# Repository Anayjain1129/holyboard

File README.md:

# Orpheus-Pad

### Why did I make it?
I made it because I want keeb so bed and my keyboar has stop working😭, So, I though I can make it through highway.

### What was the hardest part about this ?
Getting two keebs rejected was the hardest part I hope this one get approved.

Features:

- OLED for Capslock and numpad
- 80x keys
- Raspberry Pi Pico
- Customised layout
- QMK firmware
- HackClub Branded PCB
- Custom case

### Schematic

### PCB 

### Case

The space which is remaining and is empty is intetional cause i will be using stickers there

- Side

I made some asthetics for my custom keeb. Like I have added holes on all the sides to make it look more good

### 3D view of all parts together 

link to full 3d thing-
https://cad.onshape.com/documents/cac1d933657028d584a203ec/w/4e6a3fc25500be93378999df/e/b6dbc2fcb8cb6ab38fa48a89?renderMode=0&uiState=688a702c2d96e6706e64265e

A special thanks to Kai, Aditya, Mohid and The-Wolf and big thanks to alex who is helping me to make my projects better. 💓

## BOM

| Name                                                          | Qty | Final Price - INR (USD) | Link                                                                                                                        |
| ------------------------------------------------------------- | --- | ----------------------- | ----------------------------------------------------------------------------------------------------------                  |
| Gateron EF Grayish                                            | 80  | 1560 ($18.19)           | [here](https://neomacro.in/products/gateron-ef-grayish)                                                                     |
| Durock Smokey Screw-In Stabilizers V2 (4+1 w/ 6.25u spacebar) | 1   | 1590 ($18.58)           | [here](https://stackskb.com/store/durock-smokey-screw-in-stabilizers-v2/)                                                   |
| Cherry Profile PBT Keycaps                                    | 1   | 1300 ($15.15)           | [here](https://stackskb.com/store/veekos-gradient-keycaps-cherry-profile-135-keys)                                          |
| Diode 1N4148 Through - Hole                                   | 100 | 100 ($1.17)             | [here](https://amzn.in/d/j3eLvoh)                                                                                           |
| OLED                                                          | 1   | 166 ($1.92)             | [here]([https://amzn.in/d/hVRxzij](https://www.amazon.in/Electronic-Spices-Display-Module-Interface/dp/B0D9S3W7VM/ref=sr_1_8?sr=8-8))                                                                                           |
| M3 x 20mm Bolt                                                | 15  | 149 ($1.73)             | [here](https://amzn.in/d/8GRQWAB)                                                                                           |
| M3 Nuts                                                       | 8   | 100 ($1.16)             | [here](https://amzn.in/d/7UQtsm8)                                                                                           |
| M3 x 5mm Heatset Insert                                       | 25  | 179 ($2.09)             | [here](https://amzn.in/d/ixybuAc)                                                                                           |
| PCB - (Black Color)                                           | 5   | 6037 ($69.99)           ||
| Raspberry Pi Pico                                             | 1   | 449 ($5.19)             | [here](http://amazon.in/Raspberry-Pi-Headers-Soldered-Micro/dp/B08WPNM7JB/ref=sr_1_2?sr=8-2)                                |
| Case- top,mid,bot                                             | 1   | Print Legion

## Total Pricing
The total price comes out to be 11,660.13 INR ($135.17)

The pricing might slightly vary due to flash sales, and dollar market trends.

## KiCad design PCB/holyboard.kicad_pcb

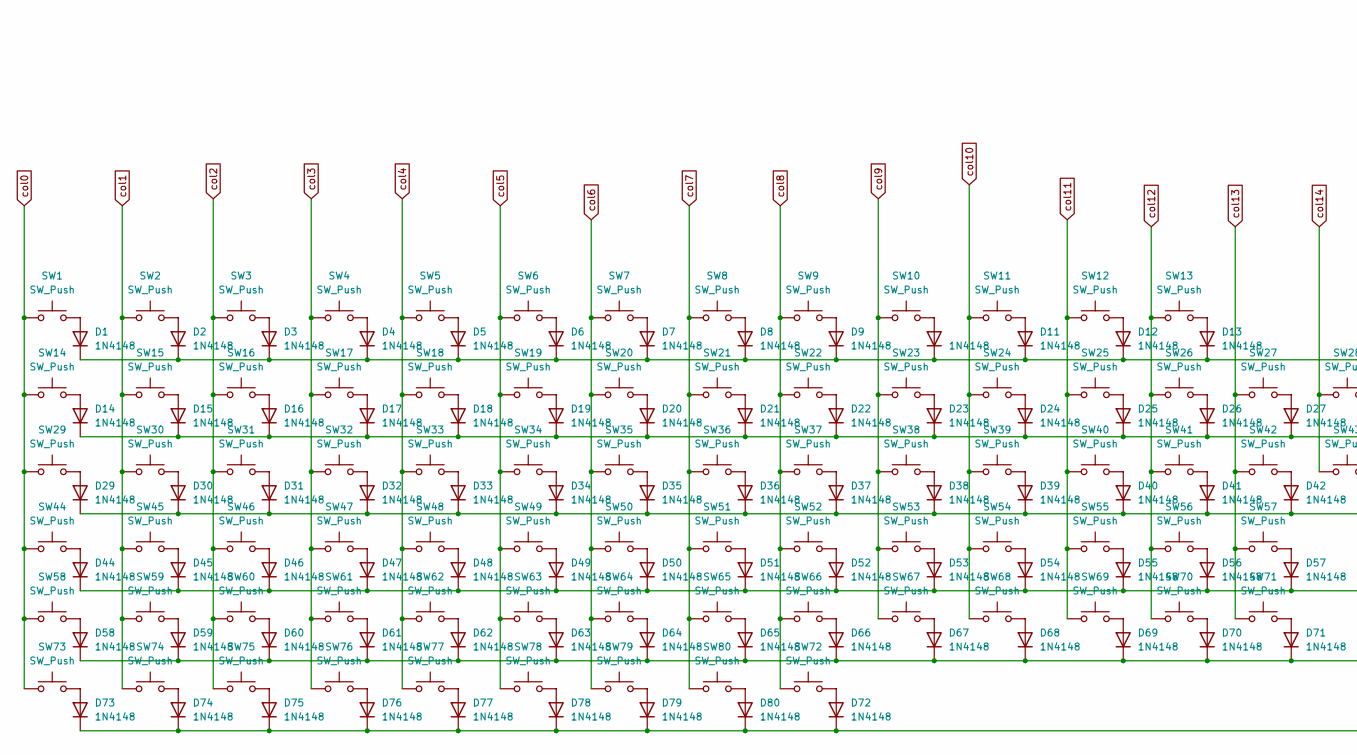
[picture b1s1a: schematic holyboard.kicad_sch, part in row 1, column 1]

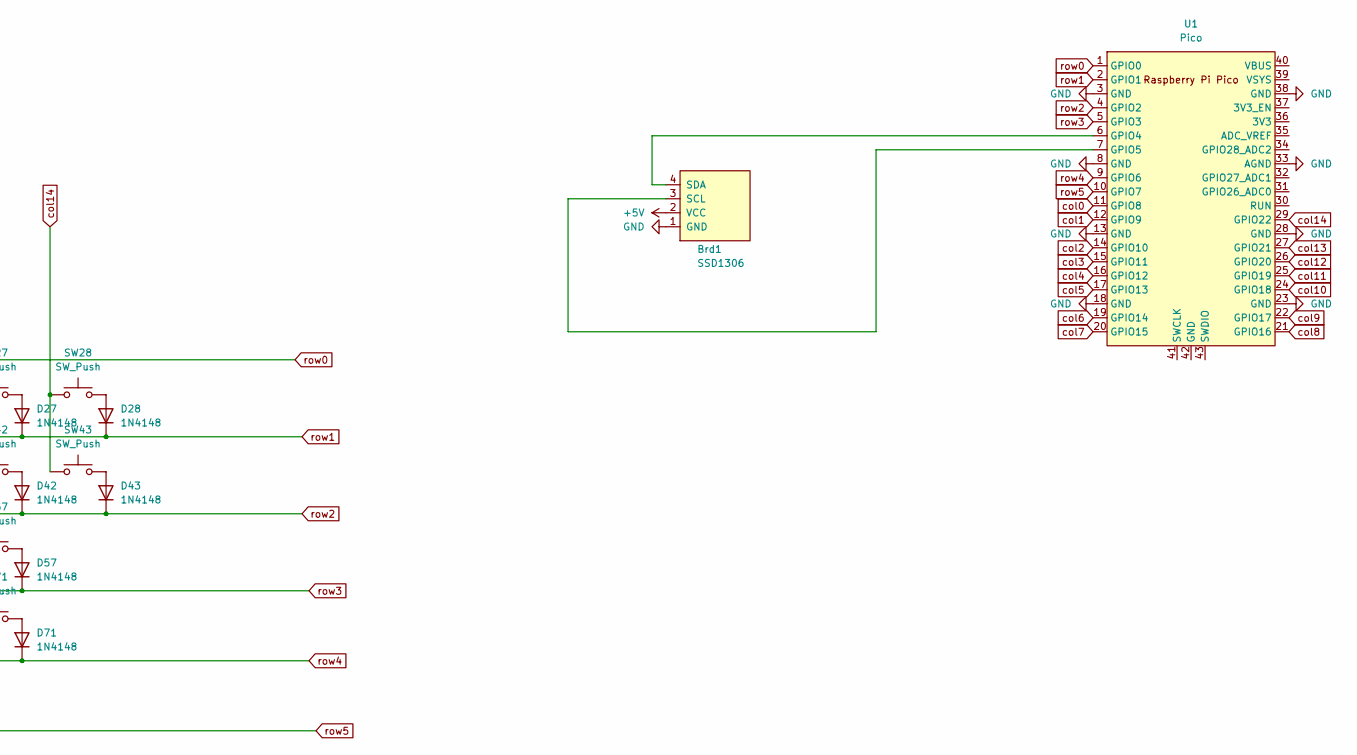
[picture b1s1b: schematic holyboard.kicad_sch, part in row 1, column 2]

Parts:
Brd1: SSD1306; SSD1306-0.91-OLED-4pin-128x32
D1, D2, D3, D4, D5, D6, D7, D8, D9, D10, D11, D12, D13, D14, D15, D16, D17, D18, D19, D20, D21, D22, D23, D24, D25, D26, D27, D28, D29, D30, D31, D32, D33, D34, D35, D36, D37, D38, D39, D40, D41, D42, D43, D44, D45, D46, D47, D48, D49, D50, D51, D52, D53, D54, D55, D56, D57, D58, D59, D60, D61, D62, D63, D64, D65, D66, D67, D68, D69, D70, D71, D72, D73, D74, D75, D76, D77, D78, D79, D80: 1N4148; D_DO-35_SOD27_P7.62mm_Horizontal
SW1, SW2, SW3, SW4, SW5, SW6, SW7, SW8, SW9, SW10, SW11, SW12, SW13, SW14, SW15, SW16, SW17, SW18, SW19, SW20, SW21, SW22, SW23, SW24, SW25, SW26, SW28, SW30, SW31, SW32, SW33, SW34, SW35, SW36, SW37, SW38, SW39, SW40, SW41, SW43, SW45, SW46, SW47, SW48, SW49, SW50, SW51, SW52, SW53, SW54, SW55, SW57, SW59, SW60, SW61, SW62, SW63, SW64, SW65, SW66, SW67, SW68, SW70, SW71, SW78, SW79, SW80: SW_Push; SW_Cherry_MX_1.00u_PCB
SW27: SW_Push; SW_Cherry_MX_2.00u_PCB
SW29, SW42: SW_Push; SW_Cherry_MX_1.50u_PCB
SW44, SW69: SW_Push; SW_Cherry_MX_1.75u_PCB
SW56, SW58: SW_Push; SW_Cherry_MX_2.25u_PCB
SW72, SW73, SW74, SW76, SW77: SW_Push; SW_Cherry_MX_1.25u_PCB
SW75: SW_Push; SW_Cherry_MX_6.25u_PCB
U1: Pico; RPi_Pico_SMD_TH

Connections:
+5V: Brd1.2 (VCC)
GND: Brd1.1 (GND), U1.3 (GND), U1.8 (GND), U1.13 (GND), U1.18 (GND), U1.23 (GND), U1.28 (GND), U1.33 (AGND), U1.38 (GND)
unnamed: Brd1.3 (SCL), U1.7 (GPIO5)
unnamed: Brd1.4 (SDA), U1.6 (GPIO4)
unnamed: D1.2 (A), SW1.2
unnamed: D2.2 (A), SW2.2
unnamed: D3.2 (A), SW3.2
unnamed: D4.2 (A), SW4.2
unnamed: D5.2 (A), SW5.2
unnamed: D6.2 (A), SW6.2
unnamed: D7.2 (A), SW7.2
unnamed: D8.2 (A), SW8.2
unnamed: D9.2 (A), SW9.2
unnamed: D10.2 (A), SW10.2
unnamed: D11.2 (A), SW11.2
unnamed: D12.2 (A), SW12.2
unnamed: D13.2 (A), SW13.2
unnamed: D14.2 (A), SW14.2
unnamed: D15.2 (A), SW15.2
unnamed: D16.2 (A), SW16.2
unnamed: D17.2 (A), SW17.2
unnamed: D18.2 (A), SW18.2
unnamed: D19.2 (A), SW19.2
unnamed: D20.2 (A), SW20.2
unnamed: D21.2 (A), SW21.2
unnamed: D22.2 (A), SW22.2
unnamed: D23.2 (A), SW23.2
unnamed: D24.2 (A), SW24.2
unnamed: D25.2 (A), SW25.2
unnamed: D26.2 (A), SW26.2
unnamed: D27.2 (A), SW27.2
unnamed: D28.2 (A), SW28.2
unnamed: D29.2 (A), SW29.2
unnamed: D30.2 (A), SW30.2
unnamed: D31.2 (A), SW31.2
unnamed: D32.2 (A), SW32.2
unnamed: D33.2 (A), SW33.2
unnamed: D34.2 (A), SW34.2
unnamed: D35.2 (A), SW35.2
unnamed: D36.2 (A), SW36.2
unnamed: D37.2 (A), SW37.2
unnamed: D38.2 (A), SW38.2
unnamed: D39.2 (A), SW39.2
unnamed: D40.2 (A), SW40.2
unnamed: D41.2 (A), SW41.2
unnamed: D42.2 (A), SW42.2
unnamed: D43.2 (A), SW43.2
unnamed: D44.2 (A), SW44.2
unnamed: D45.2 (A), SW45.2
unnamed: D46.2 (A), SW46.2
unnamed: D47.2 (A), SW47.2
unnamed: D48.2 (A), SW48.2
unnamed: D49.2 (A), SW49.2
unnamed: D50.2 (A), SW50.2
unnamed: D51.2 (A), SW51.2
unnamed: D52.2 (A), SW52.2
unnamed: D53.2 (A), SW53.2
unnamed: D54.2 (A), SW54.2
unnamed: D55.2 (A), SW55.2
unnamed: D56.2 (A), SW56.2
unnamed: D57.2 (A), SW57.2
unnamed: D58.2 (A), SW58.2
unnamed: D59.2 (A), SW59.2
unnamed: D60.2 (A), SW60.2
unnamed: D61.2 (A), SW61.2
unnamed: D62.2 (A), SW62.2
unnamed: D63.2 (A), SW63.2
unnamed: D64.2 (A), SW64.2
unnamed: D65.2 (A), SW65.2
unnamed: D66.2 (A), SW66.2
unnamed: D67.2 (A), SW67.2
unnamed: D68.2 (A), SW68.2
unnamed: D69.2 (A), SW69.2
unnamed: D70.2 (A), SW70.2
unnamed: D71.2 (A), SW71.2
unnamed: D72.2 (A), SW72.2
unnamed: D73.2 (A), SW73.2
unnamed: D74.2 (A), SW74.2
unnamed: D75.2 (A), SW75.2
unnamed: D76.2 (A), SW76.2
unnamed: D77.2 (A), SW77.2
unnamed: D78.2 (A), SW78.2
unnamed: D79.2 (A), SW79.2
unnamed: D80.2 (A), SW80.2
col0: SW1.1, SW14.1, SW29.1, SW44.1, SW58.1, SW73.1, U1.11 (GPIO8)
col1: SW2.1, SW15.1, SW30.1, SW45.1, SW59.1, SW74.1, U1.12 (GPIO9)
col2: SW3.1, SW16.1, SW31.1, SW46.1, SW60.1, SW75.1, U1.14 (GPIO10)
col3: SW4.1, SW17.1, SW32.1, SW47.1, SW61.1, SW76.1, U1.15 (GPIO11)
col4: SW5.1, SW18.1, SW33.1, SW48.1, SW62.1, SW77.1, U1.16 (GPIO12)
col5: SW6.1, SW19.1, SW34.1, SW49.1, SW63.1, SW78.1, U1.17 (GPIO13)
col6: SW7.1, SW20.1, SW35.1, SW50.1, SW64.1, SW79.1, U1.19 (GPIO14)
col7: SW8.1, SW21.1, SW36.1, SW51.1, SW65.1, SW80.1, U1.20 (GPIO15)
col8: SW9.1, SW22.1, SW37.1, SW52.1, SW66.1, SW72.1, U1.21 (GPIO16)
col9: SW10.1, SW23.1, SW38.1, SW53.1, SW67.1, U1.22 (GPIO17)
col10: SW11.1, SW24.1, SW39.1, SW54.1, SW68.1, U1.24 (GPIO18)
col11: SW12.1, SW25.1, SW40.1, SW55.1, SW69.1, U1.25 (GPIO19)
col12: SW13.1, SW26.1, SW41.1, SW56.1, SW70.1, U1.26 (GPIO20)
col13: SW27.1, SW42.1, SW57.1, SW71.1, U1.27 (GPIO21)
col14: SW28.1, SW43.1, U1.29 (GPIO22)
row0: D1.1 (K), D2.1 (K), D3.1 (K), D4.1 (K), D5.1 (K), D6.1 (K), D7.1 (K), D8.1 (K), D9.1 (K), D10.1 (K), D11.1 (K), D12.1 (K), D13.1 (K), U1.1 (GPIO0)
row1: D14.1 (K), D15.1 (K), D16.1 (K), D17.1 (K), D18.1 (K), D19.1 (K), D20.1 (K), D21.1 (K), D22.1 (K), D23.1 (K), D24.1 (K), D25.1 (K), D26.1 (K), D27.1 (K), D28.1 (K), U1.2 (GPIO1)
row2: D29.1 (K), D30.1 (K), D31.1 (K), D32.1 (K), D33.1 (K), D34.1 (K), D35.1 (K), D36.1 (K), D37.1 (K), D38.1 (K), D39.1 (K), D40.1 (K), D41.1 (K), D42.1 (K), D43.1 (K), U1.4 (GPIO2)
row3: D44.1 (K), D45.1 (K), D46.1 (K), D47.1 (K), D48.1 (K), D49.1 (K), D50.1 (K), D51.1 (K), D52.1 (K), D53.1 (K), D54.1 (K), D55.1 (K), D56.1 (K), D57.1 (K), U1.5 (GPIO3)
row4: D58.1 (K), D59.1 (K), D60.1 (K), D61.1 (K), D62.1 (K), D63.1 (K), D64.1 (K), D65.1 (K), D66.1 (K), D67.1 (K), D68.1 (K), D69.1 (K), D70.1 (K), D71.1 (K), U1.9 (GPIO6)
row5: D72.1 (K), D73.1 (K), D74.1 (K), D75.1 (K), D76.1 (K), D77.1 (K), D78.1 (K), D79.1 (K), D80.1 (K), U1.10 (GPIO7)

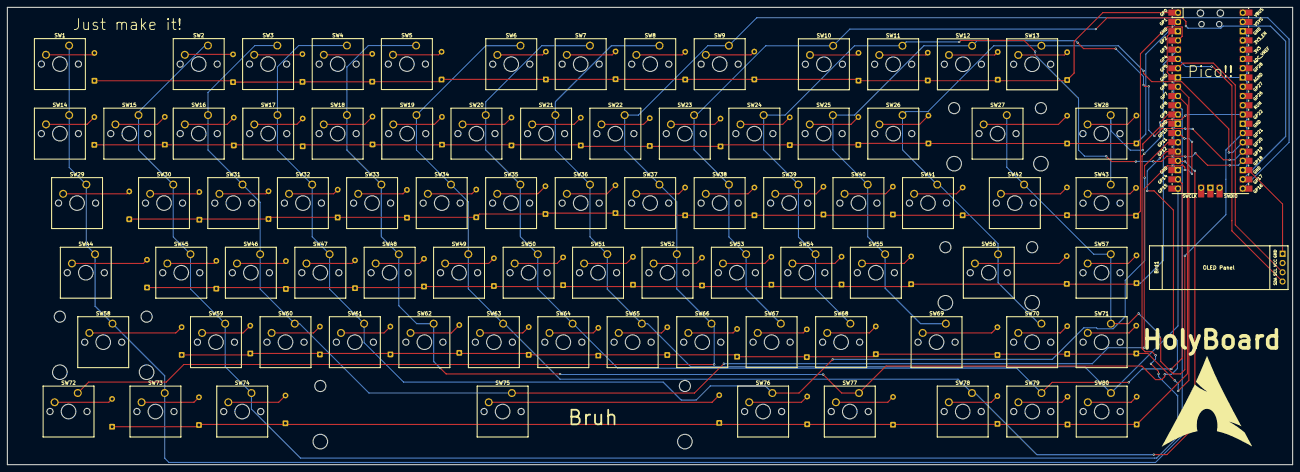
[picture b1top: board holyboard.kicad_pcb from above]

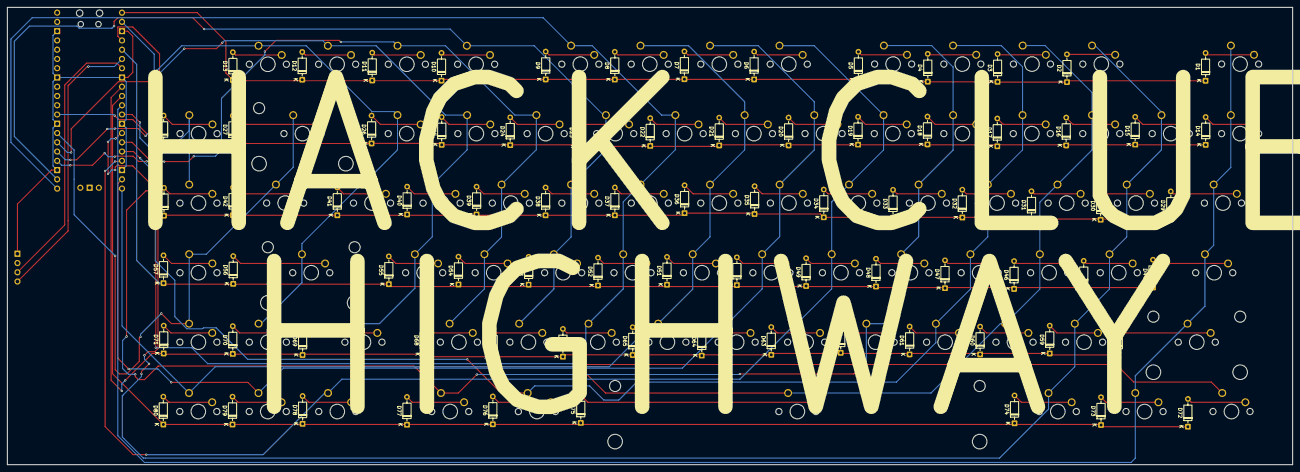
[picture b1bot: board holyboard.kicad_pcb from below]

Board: 2 copper layers, 352.5 x 125.4 mm, 162 parts (80 on the bottom side), 104 nets.

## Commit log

2025-07-18 Create nill
